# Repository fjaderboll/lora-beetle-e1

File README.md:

# Beetle E1 - LoRa environment sensor

* LoRaWAN implementation
* Measures:
	* Temperature
	* Humidity
	* Pressure
	* Light
* Rechargeable battery (via USB)
	* Up to 3 years of battery life ([details](doc/battery.md))
* Weather proof case

## Hardware components
* [CubeCell HTCC-AB01_V2](https://docs.heltec.cn/en/node/asr650x/htcc_ab01/) with antenna
* BME280 (temperature, humidity, pressure sensor)
* BH1750 (light sensor)
* Lithium-ion battery 3.7V (18650)
* Battery holder
* [Circuit board](board/README.md)
* [Case](case/README.md)

See [cost](doc/cost.md) for estimated pricing.

## Software setup
See [software](doc/software.md) with instructions how to flash the *CubeCell*.

## Receive and send data
* [Uplinks](doc/uplink.md)
* [Downlinks](doc/downlink.md)

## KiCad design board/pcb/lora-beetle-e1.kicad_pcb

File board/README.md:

# Circuit board

## Wiring

Both sensors share the CubeCell I²C bus and are powered from the switched
Vext output on header J2 (pin 4, labelled `Ve`).

| From (CubeCell J2) | BME280 (GY-BME280) | BH1750 (GY-302) | Wire colour |
|--------------------|--------------------|-----------------|-------------|
| Pin 4 `Ve` (Vext)  | `VCC`              | `VCC`           | red         |
| Pin 1 `GND`        | `GND`              | `GND`           | black       |
| Pin 6 `SCL`        | `SCL`              | `SCL`           | green       |
| Pin 7 `SDA`        | `SDA`              | `SDA`           | blue        |
| Pin 1 `GND`        | –                  | `ADDR`          | black       |
| –                  | `CSB`, `SDO`: not connected | –      | –           |

Notes:
* Vext is switched by the firmware (GPIO6, `Vext` LOW = on). It is turned off
  between uplinks so the sensors draw no current in deep sleep.
* The BH1750 `ADDR` pin is tied to GND, which gives I²C address `0x23`. The
  GY-302 module has its own pull-down, but a hard GND does not depend on it.
* The BME280 `CSB`/`SDO` pins are left open. The module's pull-ups select I²C
  mode; the firmware tries both `0x76` and `0x77`.
* The 18650 holder is wired to the `BAT` header on the carrier board. A short
  JST 1.25 lead goes from there to the CubeCell's battery socket on its
  underside. The battery is charged through the CubeCell's USB-C port.

## Carrier board

*See here for initial [prototype](prototype.md).*

A 56 × 101 mm two-layer board. The 18650 holder runs along the left edge.
The CubeCell, BH1750 and BME280 sit in a column beside it, with the CubeCell's
USB-C port at the board edge. All parts go on the top side, and every module
plugs into female pin headers.

| Ref  | Part                                   | Footprint                 |
|------|----------------------------------------|---------------------------|
| BT1  | Keystone 1042P 18650 holder (SMD)      | SMD pads + locating holes |
| J1   | Battery header (`+` / `−`)             | 1×2 male, 2.54 mm         |
| J2   | CubeCell header J2                     | 1×11 female, 2.54 mm      |
| J3   | CubeCell header J3 (mechanical, GND)   | 1×11 female, 2.54 mm      |
| J4   | BME280 module (GY-BME280)              | 1×6 female, 2.54 mm       |
| J5   | BH1750 module (GY-302)                 | 1×5 female, 2.54 mm       |
| H1–4 | Mounting holes                         | M3 (3.2 mm)               |

Routing (red = top layer, blue = bottom layer, GND pours hidden):

* SCL is on the top layer. Vext is on the bottom layer. SDA starts on the top
  layer and drops through a via to the bottom. The top render above only shows
  SCL. The other traces are underneath.
* GND has no traces. Every GND pad (CubeCell J2-1, J2-5 and J3-1, each
  sensor's `GND`, and the BH1750 `ADDR`) connects to the copper pour on both
  layers.
* The battery nets only connect the holder to J1. They are not joined to GND on
  the board, because the CubeCell does that through the JST lead.

See [Assembly](#assembly) for how to put it together.

### Ordering from PCBWay

Upload [`pcb/lora-beetle-e1-gerbers.zip`](pcb/lora-beetle-e1-gerbers.zip).
The defaults work: 2 layers, 1.6 mm FR-4, 1 oz copper, HASL, no stencil.
Minimum track and gap is 0.25 mm, and the smallest hole is the 0.4 mm via.

### Editing

The board is generated by [`pcb/build_pcb.py`](pcb/build_pcb.py). Change the
script, not the `.kicad_pcb` file, then run:

```shell
board/pcb/build.sh
```

This needs Docker; it runs KiCad 9 from the `kicad/kicad` image. It rebuilds
`lora-beetle-e1.kicad_pcb`, runs DRC, and exports the Gerbers, drill file, zip
and the renders in `images/`. You can open `pcb/lora-beetle-e1.kicad_pro` in
KiCad 9 to inspect the board.

## Assembly

Besides the board and the parts in the table above, you need:
* The CubeCell, BME280 and BH1750 modules, with the male pin headers that come
  with them.
* The JST 1.25 battery lead (that comes with the CubeCell), a 1×2 female pin
  header and corresponding crimp connectors.
* An 18650 battery cell.

Use standard 8.5 mm tall female headers. The case is designed for that height.

### Soldering

1. **Battery header (J1).**
  Push the short pins of the 1×2 male header into the board from the top, and
  solder them from below.
2. **Component headers (J2–J5).**
  Solder each of the female headers onto the board.
3. **Battery holder (BT1).**
  Prepare the holder with tin on the underside of the pads. Place the holder on
  its outline with the pegs in the locating holes. Heat the two pads until
  the tin underneath melts.
4. **Components (U1-U3).**
  Solder male pins onto each module and consider their final orientation:
   * **CubeCell (J2, J3):** USB-C/antenna side up
   * **BH1750 (J5):** sensor side up
   * **BME280 (J4):** sensor side up
5. **Check the board.**
  With nothing plugged in, check with a multimeter that
  there is no connection between `VCC` and `GND`, between `SCL` and `SDA`,
  or between `+` and `−` on J1. `ADDR` and `GND` on J5 are meant to be
  connected.

### Putting it together

1. **Battery lead**
  Use a crimping tool to attach the 1×2 female pin header to the open end of
  the battery lead.
2. **Battery.**
  Put the cell in the holder, make sure to check the polarity.
3. **Sensors.**
  Plug the BH1750 into J5 and the BME280 into J4, facing in the direction of
  the outline on the board.
4. **Antenna.**
  Connect the LoRa antenna to the CubeCell. Don't power the
  CubeCell without it, because transmitting without an antenna can damage
  the radio.
5. **CubeCell.**
  Plug the JST end of the lead into the battery socket on the
  underside of the CubeCell. Then press the CubeCell into J2 and J3, with
  USB-C facing down, and the battery lead extending upwards.
6. **Power.**
  Push the lead's female header onto J1, `+` to `+`. The CubeCell
  starts up. Flash the firmware as described in
  [software setup](../doc/software.md#setup), and charge the cell through
  the USB-C port.
7. **Case.**
  Fit the board in the case, see [Case assembly](../case/README.md#assembly).

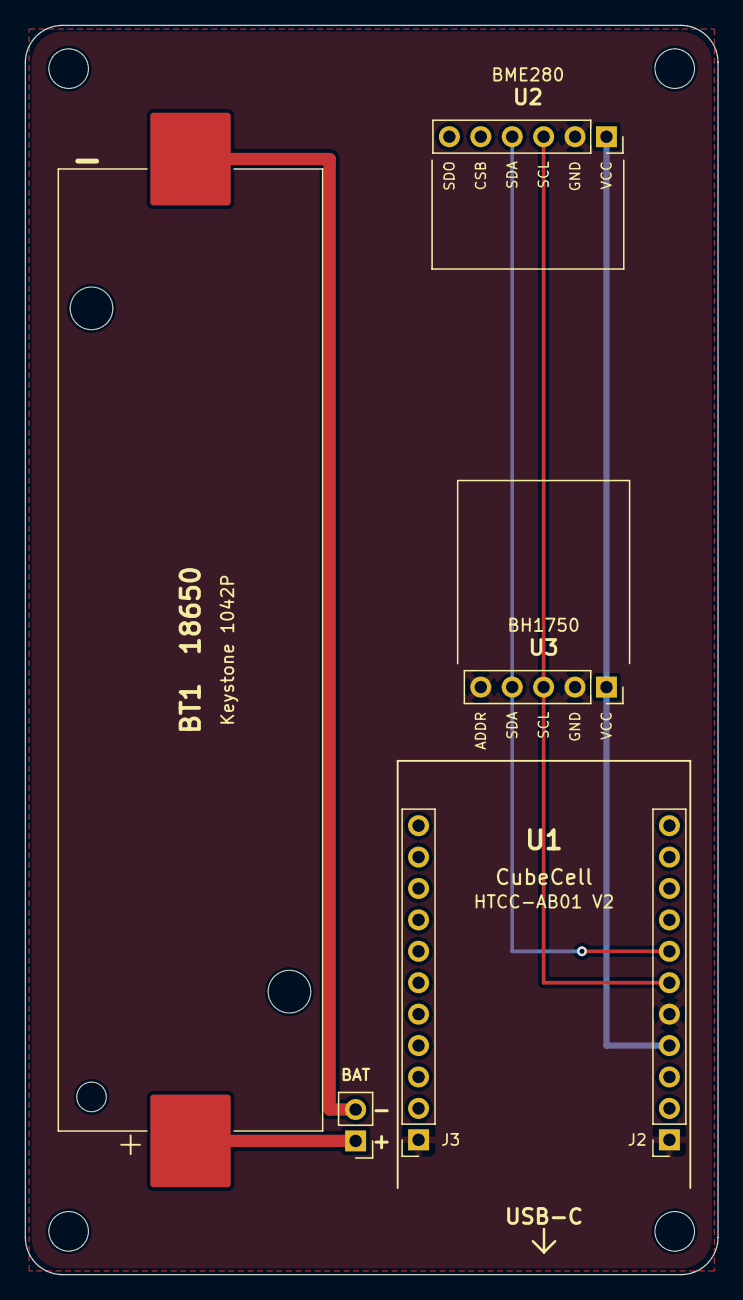
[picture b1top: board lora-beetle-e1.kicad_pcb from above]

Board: 2 copper layers, 56.0 x 101.0 mm, 10 parts (0 on the bottom side), 6 nets.

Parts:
BT1: Keystone 1042P 18650; BatteryHolder_Keystone_1042_1x18650
H1, H2, H3, H4: M3; MountingHole_3.2mm_M3
J1: BAT; PinHeader_1x02_P2.54mm_Vertical
J2: CubeCell J2; PinSocket_1x11_P2.54mm_Vertical
J3: CubeCell J3; PinSocket_1x11_P2.54mm_Vertical
J4: BME280 (GY-BME280); PinSocket_1x06_P2.54mm_Vertical
J5: BH1750 (GY-302); PinSocket_1x05_P2.54mm_Vertical

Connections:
BAT+: BT1.1, J1.1
BAT-: BT1.2, J1.2
GND: J2.1, J2.5, J3.1, J4.2, J5.2, J5.5
SCL: J2.6, J4.3, J5.3
SDA: J2.7, J4.4, J5.4
VEXT: J2.4, J4.1, J5.1

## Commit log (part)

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2026-05-15 First implementation
2026-05-15 README notice
2026-05-15 Mixed improvements
2026-05-15 TTN uplink decoder
2026-06-20 Doc updates
2026-06-20 Proper custom key handling
